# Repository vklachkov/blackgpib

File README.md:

# BlackGPIB

BlackGPIB is hardware that emulates GPIB disk drives for the GRiD Compass. It is based on the Raspberry Pi RP2040.

## Hardware

Hardware schematics and design files are located in the `hardware` folder. Production files are available in the [latest release](github.com/vklachkov/blackgpib/releases) on GitHub.

We recommend using the latest `pico` version. The list of components and known issues is described in the `README.md` file located in the `hardware/pico` directory.

## Firmware

The firmware source code is located in the `pico` folder.

The latest stable prebuilt firmware in UF2 format is available in the [latest release](https://github.com/vklachkov/blackgpib/releases) on GitHub.

### Flashing prebuilt firmware

To flash the firmware, hold the **BOOTSEL** button while connecting the Raspberry Pi Pico to your computer. The Pico will appear as a removable drive.

Copy the `blackgpib.uf2` file to this drive. The Pico will reboot automatically after the file is copied.

### Building firmware from source

To build the firmware yourself, install the Pico SDK first. Follow the instructions on the official Raspberry Pi website:

https://www.raspberrypi.com/documentation/microcontrollers/c_sdk.html

Then follow these steps.

1. Clone the repository:

```bash
git clone --depth 1 --recursive https://github.com/vklachkov/blackgpib
```

2. Go to the sources directory:

```bash
cd blackgpib/pico
```

3. Configure the project for your board:

```bash
cmake -S . -B build -DPICO_BOARD=pico
```

4. Build:

```bash
cmake --build build -j
```

5. Flash the firmware:

   Hold the **BOOTSEL** button while connecting the Raspberry Pi Pico to your computer. Then copy the `blackgpib.uf2` file from the `build` folder to the mounted Pico drive.

## How to use it?

After assembling and flashing the device, find a microSD card and format it as FAT32 or exFAT. Copy the disk images to this card. Insert the microSD card into BlackGPIB. Connect BlackGPIB to power, the LED should turn on after about one and a half seconds. After that, you can turn on the GRiD Compass. Enjoy!

### Which file formats are supported?

Currently, only .IMG files are supported. IMD and .CHD are not supported.

If you want to use IMD files from gridrepository.org, please use the [imd2raw](https://github.com/RetroFloppy/imd2raw) converter until BlackGPIB support is not available.

### How is the address selected?

For images that do not have a GPIB address specified in their filename, the address is selected automatically.

Floppy disk images use addresses 5, 6, and 13. Other images use the remaining default addresses (4, 5, 6, 12, 13).

If addresses conflict, or if there are no addresses left, an entry about this will be written to log.txt.

### How do I bind an image to a specific GPIB address?

Rename the image to FXX or HXX, where XX is the GPIB address. For example, FLOPPY4_TEST.IMG or HD12.IMG.

### How do I change the image geometry?

You can’t, it is selected automatically. Geometry configuration is not supported.

### Troubleshooting

**The LED is always off**

Check that you assembled the emulator correctly, powered it, and flashed the correct firmware.

**The device is steadily blinking the LED on the board**

This means that the device does not see the SD card, or the filesystem on it is not FAT.

Remove the SD card, format it again, and insert it into the device. If you did not disconnect power from BlackGPIB, then, if successful, the device will blink the LED several times, and then the LED should stay steadily on. This means that the device is ready to use.

**The device is blinking SOS**

This means that the device has gone into a boot loop. Normally, this should not happen.

Connect the device to your computer, open a serial port monitor, and check what went wrong before the boot loop. You can email me or open an issue, and I will try to help.

## License

This project is released under the [MIT License](LICENSE).

You are free to use, modify, and share it. I will be happy if BlackGPIB helps you bring your GRiD Compass back to life and use it again.

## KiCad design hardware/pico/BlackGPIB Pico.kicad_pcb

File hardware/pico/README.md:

# BlackGPIB Pico

## Components

| Part                     | Value                     | Package                  | Quantity | Comment                                                              |
|--------------------------|---------------------------|--------------------------|----------|----------------------------------------------------------------------|
| GPIB Connector Female    | -                         | 90 Degree                | 1        |                                                                      |
| SN75160                  | -                         | SMD or DIP               | 1        |                                                                      |
| SN75161 / SN75162        | -                         | SMD or DIP               | 1        |                                                                      |
| Resistor Pack (4x0603)   | 3.3kΩ                     | 1206 (4x0603)            | 2        | Front side of the board                                              |
| Resistor Pack (4x0603)   | 6.8kΩ                     | 1206 (4x0603)            | 2        | Back side of the board                                               |
| Ceramic Capacitor        | 0.1µF                     | 1206                     | 3        | Any for 5V, I used random 10V capacitor                              |
| Tantalum Capacitor       | 100µF                     | Case C (6032)            | 1        | Any for 3.3V, I used random 10V capacitor                            |
| MicroSD Card Slot        | -                         | SMD                      | 1        | [LSCS](https://www.lcsc.com/product-detail/C114218.html)             |
| Pi Pico 2040             | -                         | SMD                      | 1        |                                                                      |

## Known problems

### Rev 1

Because the Raspberry Pi Pico is positioned far from the edge of the board, not all micro-USB cables will fit.

When inserting the cable, hold it gently to prevent the SD card from popping out of the slot.

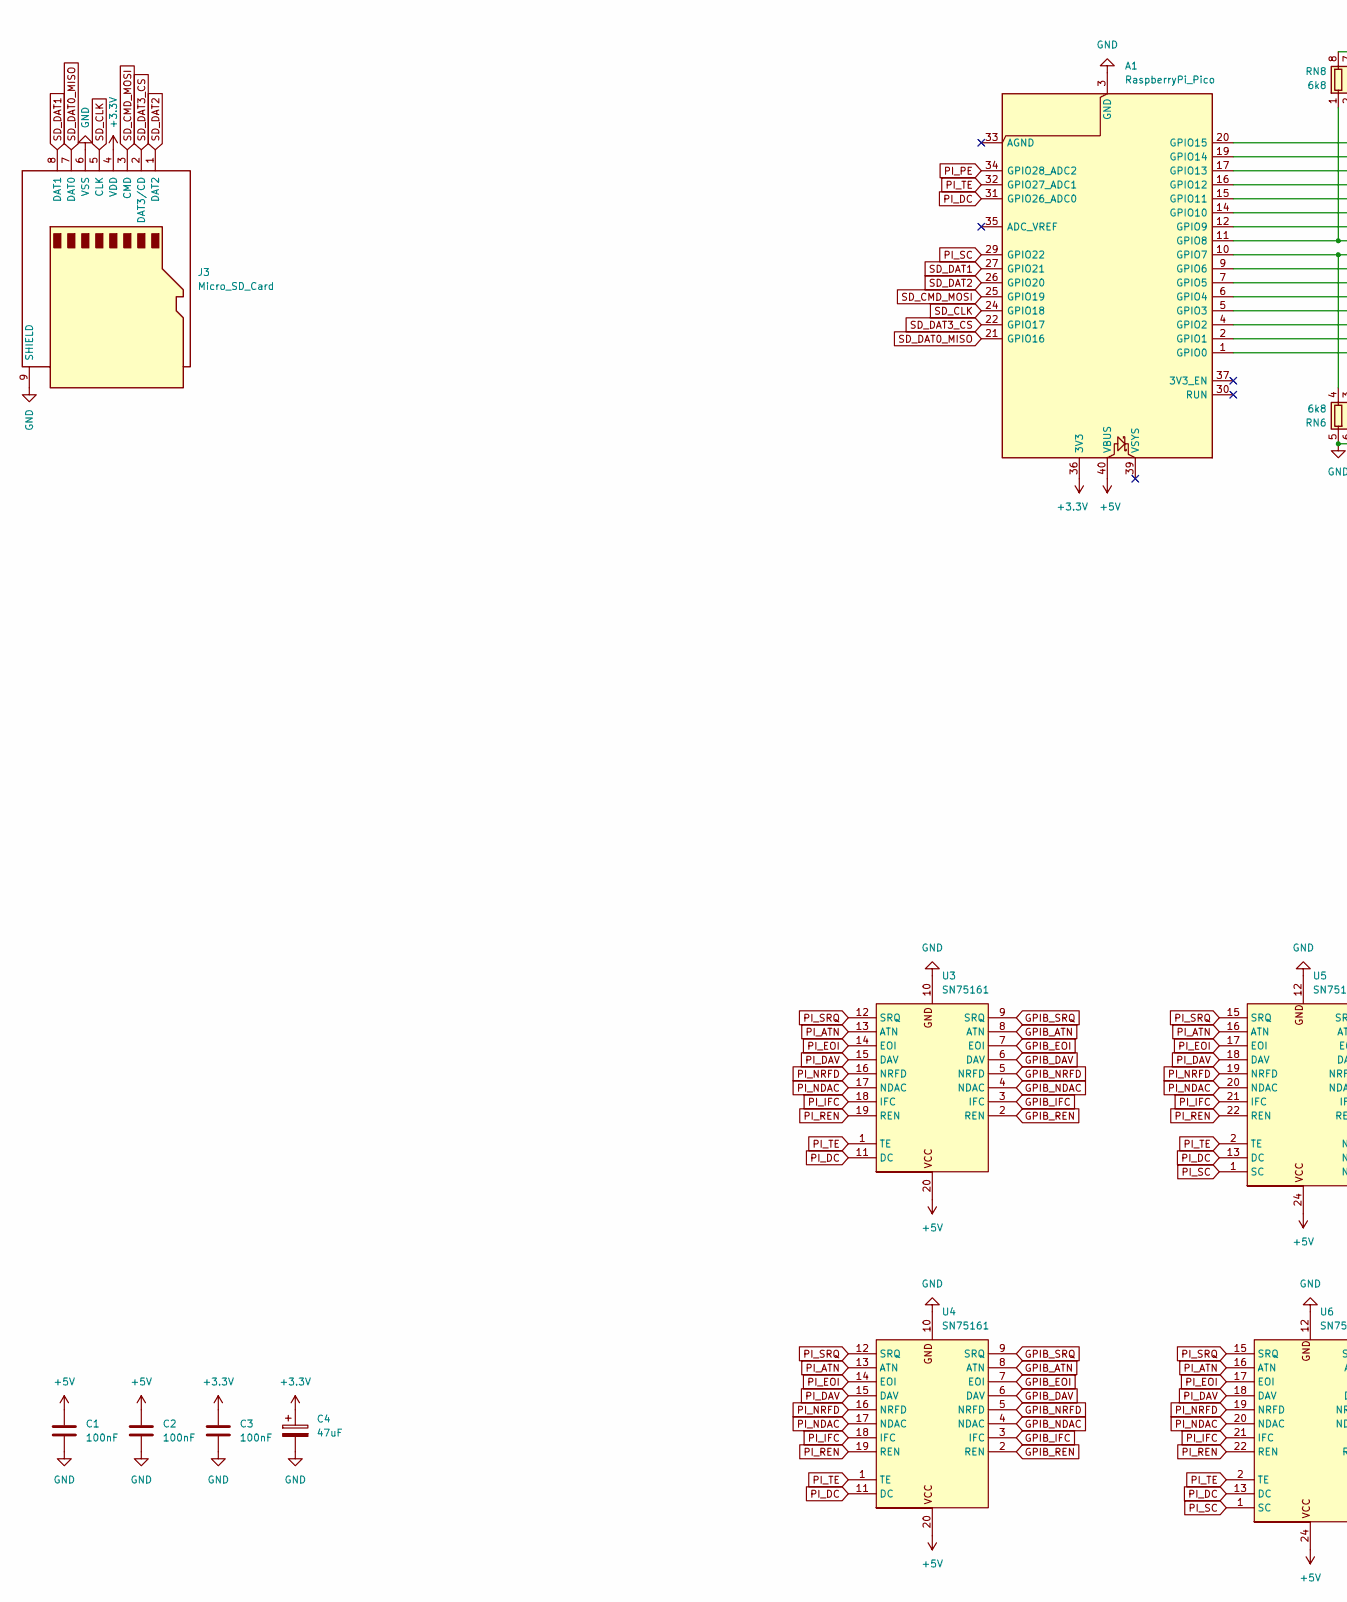
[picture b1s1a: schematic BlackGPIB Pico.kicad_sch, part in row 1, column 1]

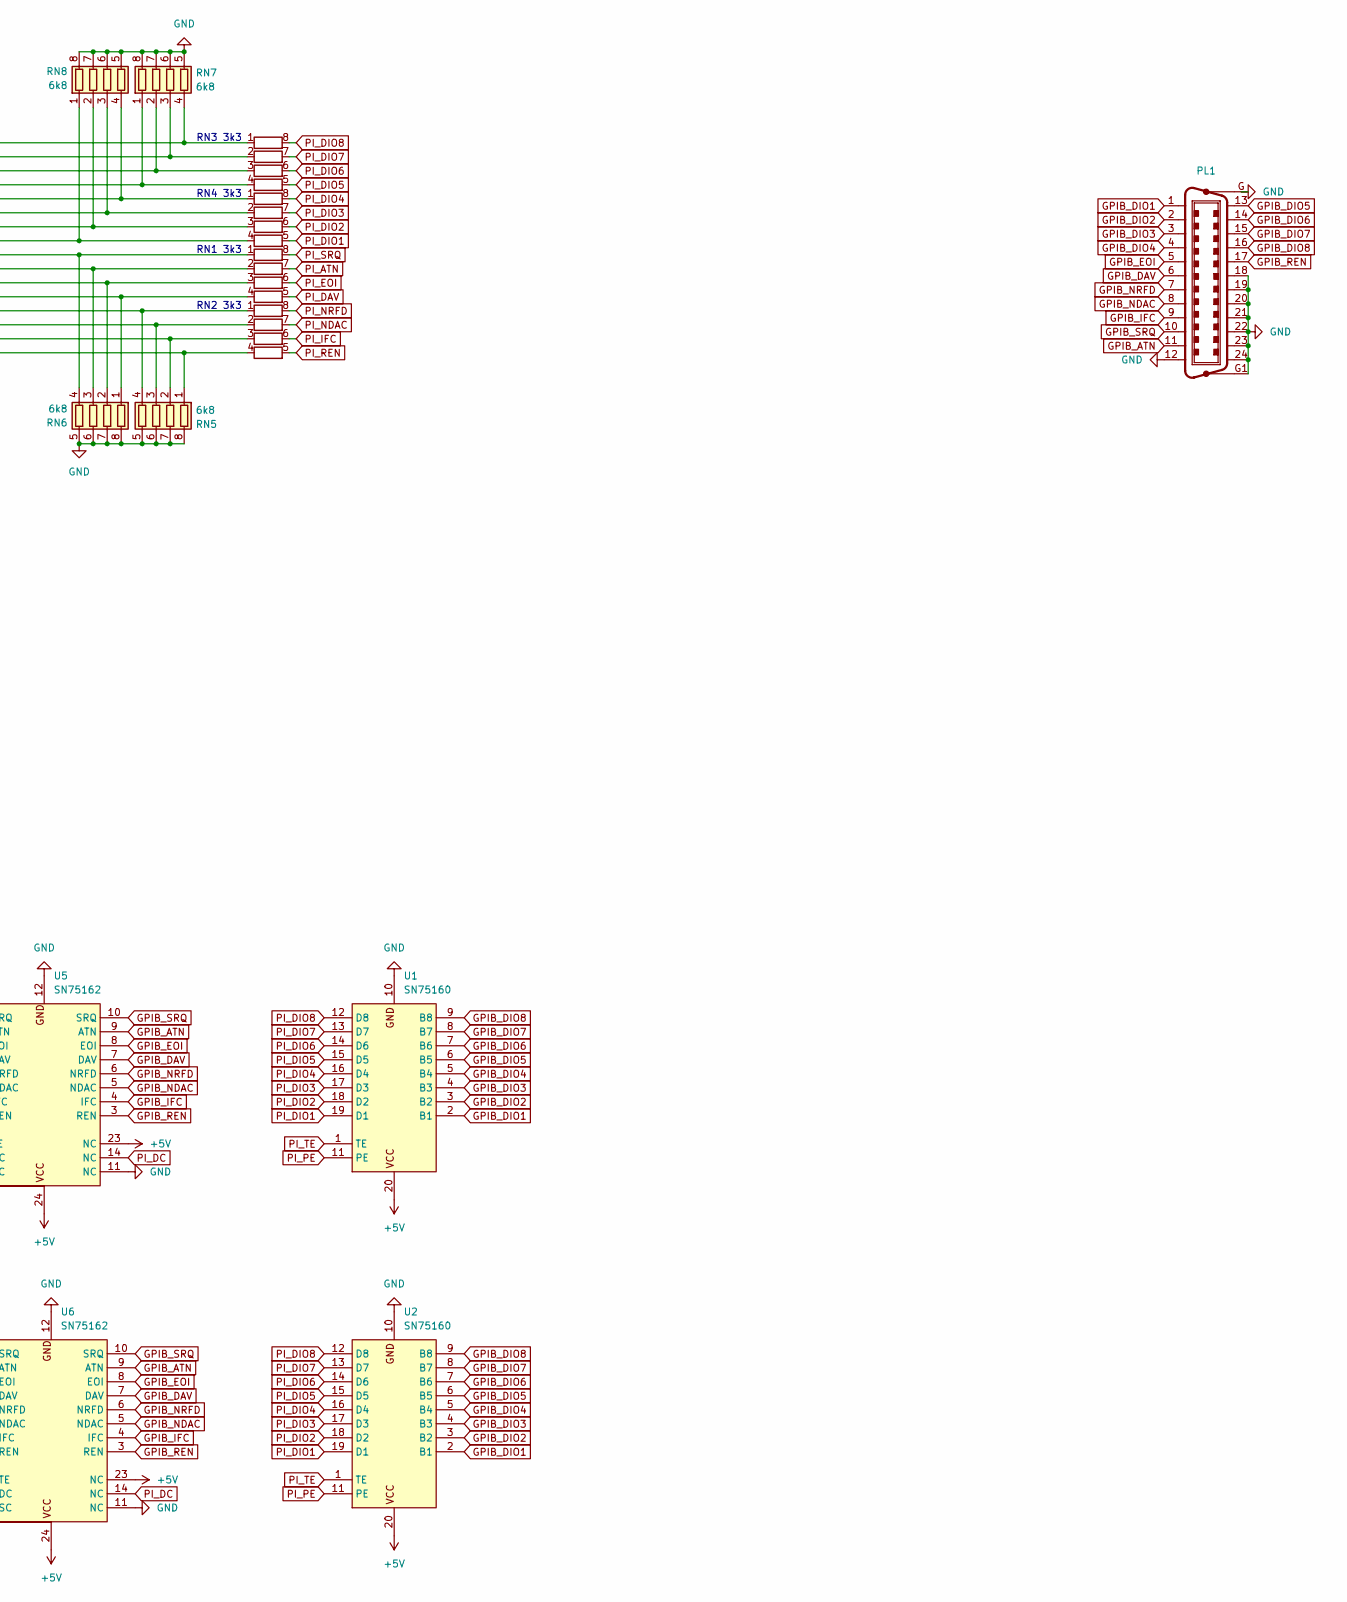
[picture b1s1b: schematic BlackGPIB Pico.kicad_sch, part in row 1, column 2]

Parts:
A1: RaspberryPi_Pico; RaspberryPi_Pico_SMD_HandSolder
C1, C2, C3: 100nF; C_1206_3216Metric_Pad1.33x1.80mm_HandSolder
C4: 47uF; CP_EIA-6032-15_Kemet-U_HandSolder
J3: Micro_SD_Card; microSD_HC_Hirose_DM3AT-SF-PEJM5
PL1: Centronics 24; Centronics-24
RN1, RN2, RN3, RN4: 3k3; R_Array_Convex_4x1206
RN5, RN6, RN7, RN8: 6k8; R_Array_Convex_4x1206
U1: SN75160; DIP-20_W7.62mm_LongPads
U2: SN75160; SOIC-20
U3: SN75161; DIP-20_W7.62mm_LongPads
U4: SN75161; SOIC-20
U5: SN75162; DIP-24_W7.62mm_LongPads
U6: SN75162; SOIC-24

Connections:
+3.3V: A1.36 (3V3), C3.1, C4.1, J3.4 (VDD)
+5V: A1.40 (VBUS), C1.1, C2.1, U1.20 (VCC), U2.20 (VCC), U3.20 (VCC), U4.20 (VCC), U5.23 (NC), U5.24 (VCC), U6.23 (NC), U6.24 (VCC)
GND: A1.3 (GND), A1.8 (GND), A1.13 (GND), A1.18 (GND), A1.23 (GND), A1.28 (GND), A1.38 (GND), C1.2, C2.2, C3.2, C4.2, J3.6 (VSS), J3.9 (SHIELD), PL1.12, PL1.18, PL1.19, PL1.20, PL1.21, PL1.22, PL1.23, PL1.24, PL1.G, PL1.G1, RN5.5 (R4.2), RN5.6 (R3.2), RN5.7 (R2.2), RN5.8 (R1.2), RN6.5 (R4.2), RN6.6 (R3.2), RN6.7 (R2.2), RN6.8 (R1.2), RN7.5 (R4.2), RN7.6 (R3.2), RN7.7 (R2.2), RN7.8 (R1.2), RN8.5 (R4.2), RN8.6 (R3.2), RN8.7 (R2.2), RN8.8 (R1.2), U1.10 (GND), U2.10 (GND), U3.10 (GND), U4.10 (GND), U5.11 (NC), U5.12 (GND), U6.11 (NC), U6.12 (GND)
GPIB_ATN: PL1.11, U3.8 (ATN), U4.8 (ATN), U5.9 (ATN), U6.9 (ATN)
GPIB_DAV: PL1.6, U3.6 (DAV), U4.6 (DAV), U5.7 (DAV), U6.7 (DAV)
GPIB_DIO1: PL1.1, U1.2 (B1), U2.2 (B1)
GPIB_DIO2: PL1.2, U1.3 (B2), U2.3 (B2)
GPIB_DIO3: PL1.3, U1.4 (B3), U2.4 (B3)
GPIB_DIO4: PL1.4, U1.5 (B4), U2.5 (B4)
GPIB_DIO5: PL1.13, U1.6 (B5), U2.6 (B5)
GPIB_DIO6: PL1.14, U1.7 (B6), U2.7 (B6)
GPIB_DIO7: PL1.15, U1.8 (B7), U2.8 (B7)
GPIB_DIO8: PL1.16, U1.9 (B8), U2.9 (B8)
GPIB_EOI: PL1.5, U3.7 (EOI), U4.7 (EOI), U5.8 (EOI), U6.8 (EOI)
GPIB_IFC: PL1.9, U3.3 (IFC), U4.3 (IFC), U5.4 (IFC), U6.4 (IFC)
GPIB_NDAC: PL1.8, U3.4 (NDAC), U4.4 (NDAC), U5.5 (NDAC), U6.5 (NDAC)
GPIB_NRFD: PL1.7, U3.5 (NRFD), U4.5 (NRFD), U5.6 (NRFD), U6.6 (NRFD)
GPIB_REN: PL1.17, U3.2 (REN), U4.2 (REN), U5.3 (REN), U6.3 (REN)
GPIB_SRQ: PL1.10, U3.9 (SRQ), U4.9 (SRQ), U5.10 (SRQ), U6.10 (SRQ)
unnamed: A1.1 (GPIO0), RN2.4 (R4.1), RN5.1 (R1.1)
unnamed: A1.2 (GPIO1), RN2.3 (R3.1), RN5.2 (R2.1)
unnamed: A1.4 (GPIO2), RN2.2 (R2.1), RN5.3 (R3.1)
unnamed: A1.5 (GPIO3), RN2.1 (R1.1), RN5.4 (R4.1)
unnamed: A1.6 (GPIO4), RN1.4 (R4.1), RN6.1 (R1.1)
unnamed: A1.7 (GPIO5), RN1.3 (R3.1), RN6.2 (R2.1)
unnamed: A1.9 (GPIO6), RN1.2 (R2.1), RN6.3 (R3.1)
unnamed: A1.10 (GPIO7), RN1.1 (R1.1), RN6.4 (R4.1)
unnamed: A1.11 (GPIO8), RN4.4 (R4.1), RN8.1 (R1.1)
unnamed: A1.12 (GPIO9), RN4.3 (R3.1), RN8.2 (R2.1)
unnamed: A1.14 (GPIO10), RN4.2 (R2.1), RN8.3 (R3.1)
unnamed: A1.15 (GPIO11), RN4.1 (R1.1), RN8.4 (R4.1)
unnamed: A1.16 (GPIO12), RN3.4 (R4.1), RN7.1 (R1.1)
unnamed: A1.17 (GPIO13), RN3.3 (R3.1), RN7.2 (R2.1)
unnamed: A1.19 (GPIO14), RN3.2 (R2.1), RN7.3 (R3.1)
unnamed: A1.20 (GPIO15), RN3.1 (R1.1), RN7.4 (R4.1)
PI_ATN: RN1.7 (R2.2), U3.13 (ATN), U4.13 (ATN), U5.16 (ATN), U6.16 (ATN)
PI_DAV: RN1.5 (R4.2), U3.15 (DAV), U4.15 (DAV), U5.18 (DAV), U6.18 (DAV)
PI_DC: A1.31 (GPIO26_ADC0), U3.11 (DC), U4.11 (DC), U5.13 (DC), U5.14 (NC), U6.13 (DC), U6.14 (NC)
PI_DIO1: RN4.5 (R4.2), U1.19 (D1), U2.19 (D1)
PI_DIO2: RN4.6 (R3.2), U1.18 (D2), U2.18 (D2)
PI_DIO3: RN4.7 (R2.2), U1.17 (D3), U2.17 (D3)
PI_DIO4: RN4.8 (R1.2), U1.16 (D4), U2.16 (D4)
PI_DIO5: RN3.5 (R4.2), U1.15 (D5), U2.15 (D5)
PI_DIO6: RN3.6 (R3.2), U1.14 (D6), U2.14 (D6)
PI_DIO7: RN3.7 (R2.2), U1.13 (D7), U2.13 (D7)
PI_DIO8: RN3.8 (R1.2), U1.12 (D8), U2.12 (D8)
PI_EOI: RN1.6 (R3.2), U3.14 (EOI), U4.14 (EOI), U5.17 (EOI), U6.17 (EOI)
PI_IFC: RN2.6 (R3.2), U3.18 (IFC), U4.18 (IFC), U5.21 (IFC), U6.21 (IFC)
PI_NDAC: RN2.7 (R2.2), U3.17 (NDAC), U4.17 (NDAC), U5.20 (NDAC), U6.20 (NDAC)
PI_NRFD: RN2.8 (R1.2), U3.16 (NRFD), U4.16 (NRFD), U5.19 (NRFD), U6.19 (NRFD)
PI_PE: A1.34 (GPIO28_ADC2), U1.11 (PE), U2.11 (PE)
PI_REN: RN2.5 (R4.2), U3.19 (REN), U4.19 (REN), U5.22 (REN), U6.22 (REN)
PI_SC: A1.29 (GPIO22), U5.1 (SC), U6.1 (SC)
PI_SRQ: RN1.8 (R1.2), U3.12 (SRQ), U4.12 (SRQ), U5.15 (SRQ), U6.15 (SRQ)
PI_TE: A1.32 (GPIO27_ADC1), U1.1 (TE), U2.1 (TE), U3.1 (TE), U4.1 (TE), U5.2 (TE), U6.2 (TE)
SD_CLK: A1.24 (GPIO18), J3.5 (CLK)
SD_CMD_MOSI: A1.25 (GPIO19), J3.3 (CMD)
SD_DAT0_MISO: A1.21 (GPIO16), J3.7 (DAT0)
SD_DAT1: A1.27 (GPIO21), J3.8 (DAT1)
SD_DAT2: A1.26 (GPIO20), J3.1 (DAT2)
SD_DAT3_CS: A1.22 (GPIO17), J3.2 (DAT3/CD)

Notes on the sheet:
RN2 3k3
RN3 3k3
RN4 3k3
RN1 3k3

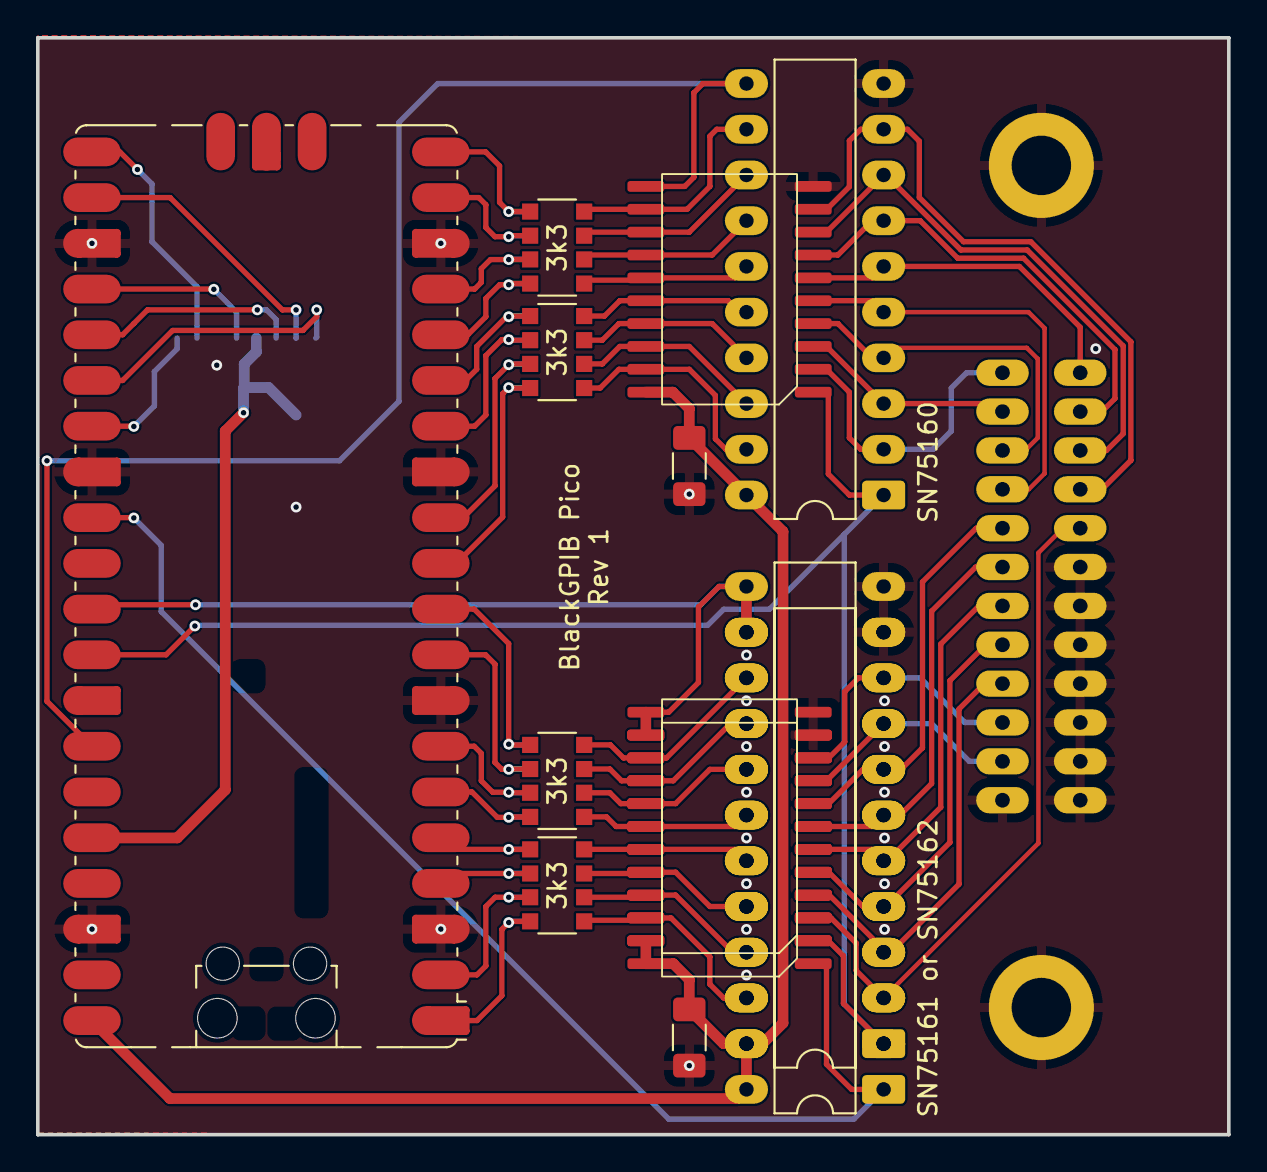
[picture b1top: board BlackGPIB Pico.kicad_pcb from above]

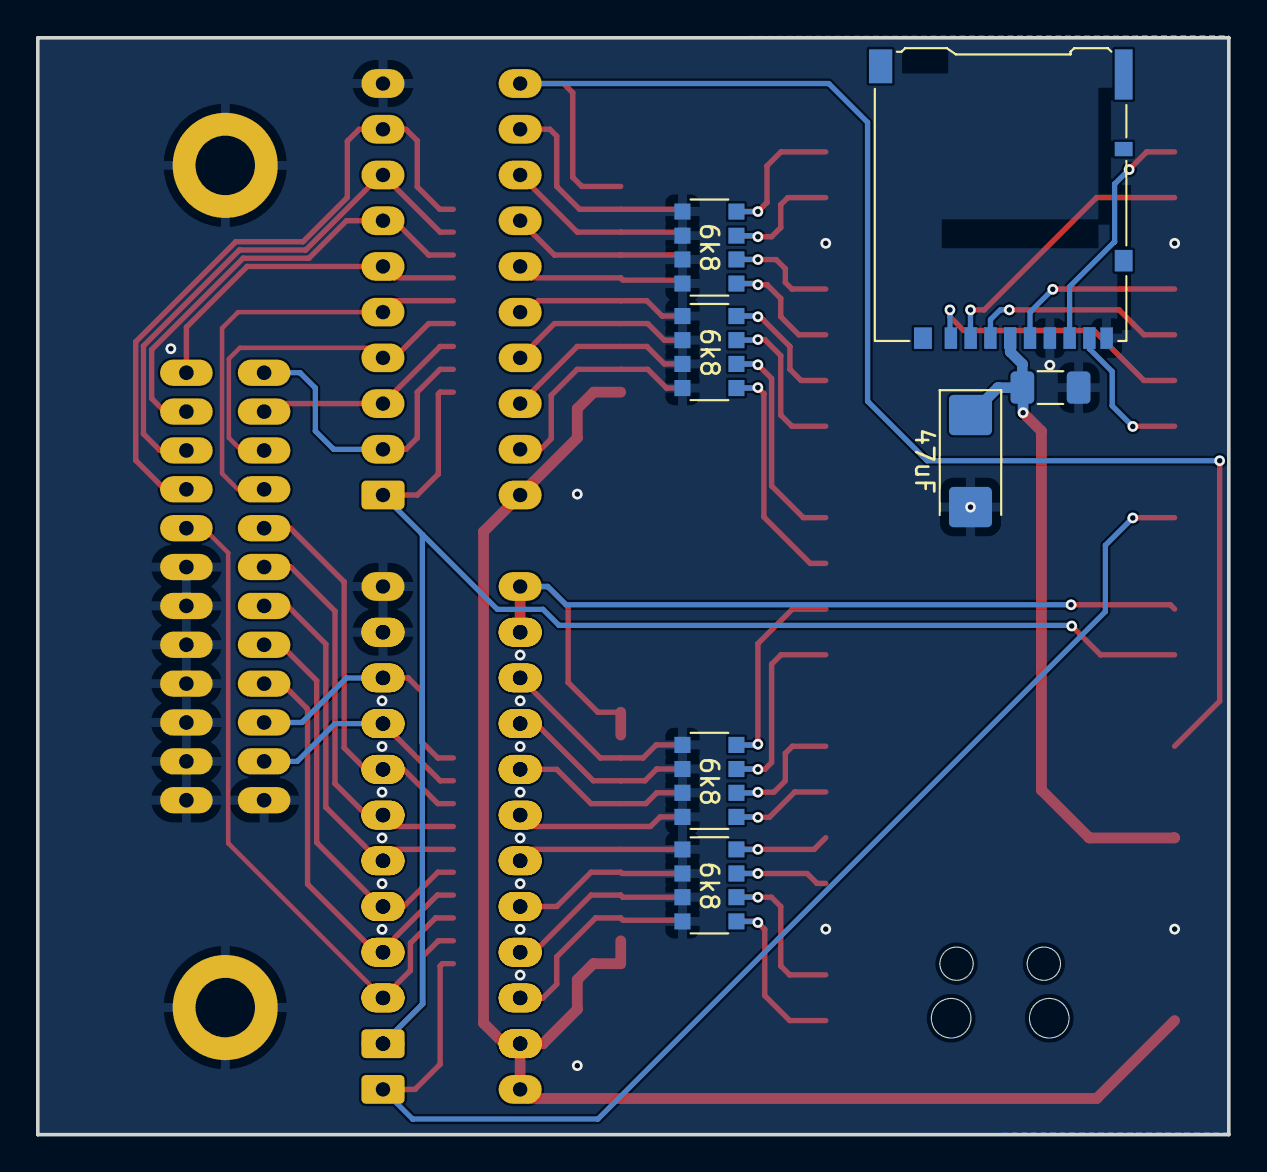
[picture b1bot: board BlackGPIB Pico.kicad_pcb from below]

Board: 2 copper layers, 66.2 x 60.9 mm, 21 parts (7 on the bottom side), 61 nets.

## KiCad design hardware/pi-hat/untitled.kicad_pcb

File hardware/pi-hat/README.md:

# First board by @JDat for Raspberry Pi 2+

This is the first revision of the board, designed by @JDat (also known as @YL3AKC):

In the photo, it's the old version with SRQ and ATN swapped.

## Components

| Part                  | Value                | Package    | Quantity |
|-----------------------|----------------------|------------|----------|
| GPIB Connector Female | -                    | 90 Degree  | 1        |
| SN75160               | -                    | SMD or DIP | 1        |
| SN75161/SN75162       | -                    | SMD or DIP | 1        |
| Resistor              | 3kΩ                  | 0805       | 20       |
| Capacitor             | 0.1uF                | 0805       | 2        |
| Pin Header            | 20x2 Straight Female | -          | 1        |

P.S. Instead of small SMD components, you can also use through-hole components, as Kirill @BOOtak Leyfer did.

https://t.me/bootaks_old_devices/286

## Errata

### Not enough space for the through-hole resistors.

As can be seen in Kirill's photo, the resistors are placed too close together, requiring them to be stacked on top of each other.

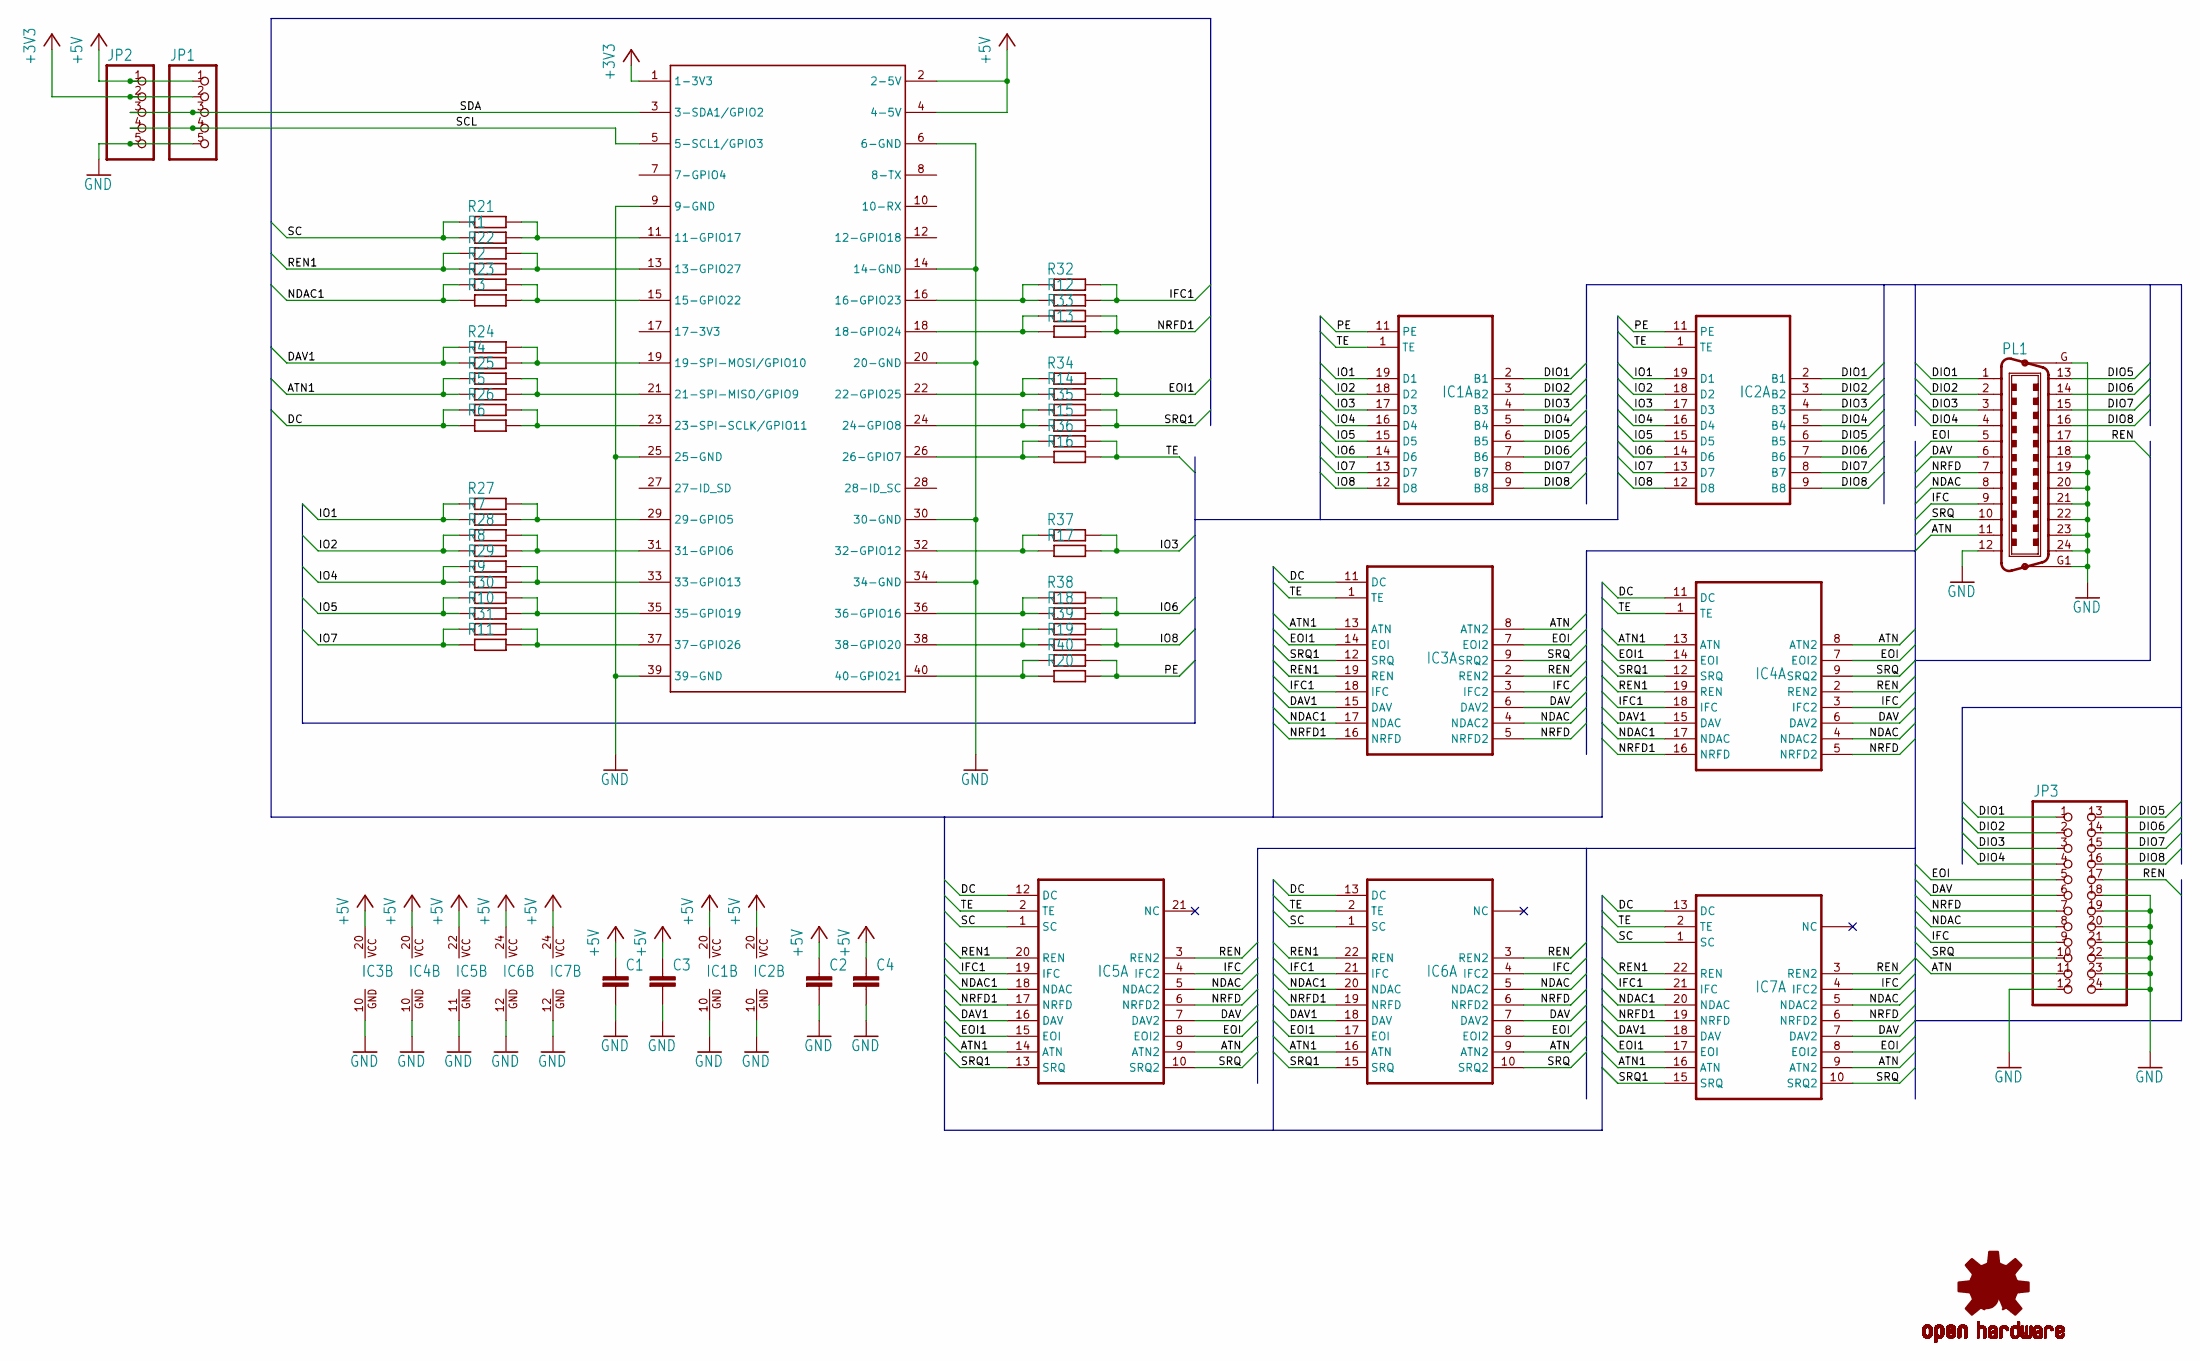
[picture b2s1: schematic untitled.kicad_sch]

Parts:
C1, C2: C-EUC0805; C0805
C3, C4: C-EU050-024X044; C050-024X044
IC1: 75160P; DIL20
IC2: 75160SO; SO20L
IC3: 75161P; DIL20
IC4: 75161SO; SO20L
IC5: 75162P; DIL22-3
IC6: 75162; DIL24-3
IC7: 75162SO24; SOIC127P1030X265-24N
JP1, JP2: PINHD-1X5; 1X05
JP3: GPIB-PINHD-2X12
LOGO2: OSHW-LOGOS; OSHW-LOGO-S
PL1: C24HP; 24HP
R1, R2, R3, R4, R5, R6, R7, R8, R9, R10, R11, R12, R13, R14, R15, R16, R17, R18, R19, R20: 3k; R0805
R21, R22, R23, R24, R25, R26, R27, R28, R29, R30, R31, R32, R33, R34, R35, R36, R37, R38, R39, R40: 3k; 0204_7
U$2: RASPBERRY-PI+HEADERONLY; RASPBERRY-PI-PLUS-HEADERONLY

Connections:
+3V3: JP1.2, JP2.2, U$2.1 (1-3V3)
+5V: C1.1, C2.1, C3.1, C4.1, IC1.20 (VCC), IC2.20 (VCC), IC3.20 (VCC), IC4.20 (VCC), IC5.22 (VCC), IC6.24 (VCC), IC7.24 (VCC), JP1.1, JP2.1, U$2.2 (2-5V), U$2.4 (4-5V)
/ATN: IC3.8 (ATN2), IC4.8 (ATN2), IC5.9 (ATN2), IC6.9 (ATN2), IC7.9 (ATN2), JP3.11, PL1.11
/ATN1: IC3.13 (ATN), IC4.13 (ATN), IC5.14 (ATN), IC6.16 (ATN), IC7.16 (ATN), R5.1, R25.1
/DAV: IC3.6 (DAV2), IC4.6 (DAV2), IC5.7 (DAV2), IC6.7 (DAV2), IC7.7 (DAV2), JP3.6, PL1.6
/DAV1: IC3.15 (DAV), IC4.15 (DAV), IC5.16 (DAV), IC6.18 (DAV), IC7.18 (DAV), R4.1, R24.1
/DC: IC3.11 (DC), IC4.11 (DC), IC5.12 (DC), IC6.13 (DC), IC7.13 (DC), R6.1, R26.1
/DIO1: IC1.2 (B1), IC2.2 (B1), JP3.1, PL1.1
/DIO2: IC1.3 (B2), IC2.3 (B2), JP3.2, PL1.2
/DIO3: IC1.4 (B3), IC2.4 (B3), JP3.3, PL1.3
/DIO4: IC1.5 (B4), IC2.5 (B4), JP3.4, PL1.4
/DIO5: IC1.6 (B5), IC2.6 (B5), JP3.13, PL1.13
/DIO6: IC1.7 (B6), IC2.7 (B6), JP3.14, PL1.14
/DIO7: IC1.8 (B7), IC2.8 (B7), JP3.15, PL1.15
/DIO8: IC1.9 (B8), IC2.9 (B8), JP3.16, PL1.16
/EOI: IC3.7 (EOI2), IC4.7 (EOI2), IC5.8 (EOI2), IC6.8 (EOI2), IC7.8 (EOI2), JP3.5, PL1.5
/EOI1: IC3.14 (EOI), IC4.14 (EOI), IC5.15 (EOI), IC6.17 (EOI), IC7.17 (EOI), R14.2, R34.2
/IFC: IC3.3 (IFC2), IC4.3 (IFC2), IC5.4 (IFC2), IC6.4 (IFC2), IC7.4 (IFC2), JP3.9, PL1.9
/IFC1: IC3.18 (IFC), IC4.18 (IFC), IC5.19 (IFC), IC6.21 (IFC), IC7.21 (IFC), R12.2, R32.2
/IO1: IC1.19 (D1), IC2.19 (D1), R7.1, R27.1
/IO2: IC1.18 (D2), IC2.18 (D2), R8.1, R28.1
/IO3: IC1.17 (D3), IC2.17 (D3), R17.2, R37.2
/IO4: IC1.16 (D4), IC2.16 (D4), R9.1, R29.1
/IO5: IC1.15 (D5), IC2.15 (D5), R10.1, R30.1
/IO6: IC1.14 (D6), IC2.14 (D6), R18.2, R38.2
/IO7: IC1.13 (D7), IC2.13 (D7), R11.1, R31.1
/IO8: IC1.12 (D8), IC2.12 (D8), R19.2, R39.2
/NDAC: IC3.4 (NDAC2), IC4.4 (NDAC2), IC5.5 (NDAC2), IC6.5 (NDAC2), IC7.5 (NDAC2), JP3.8, PL1.8
/NDAC1: IC3.17 (NDAC), IC4.17 (NDAC), IC5.18 (NDAC), IC6.20 (NDAC), IC7.20 (NDAC), R3.1, R23.1
/NRFD: IC3.5 (NRFD2), IC4.5 (NRFD2), IC5.6 (NRFD2), IC6.6 (NRFD2), IC7.6 (NRFD2), JP3.7, PL1.7
/NRFD1: IC3.16 (NRFD), IC4.16 (NRFD), IC5.17 (NRFD), IC6.19 (NRFD), IC7.19 (NRFD), R13.2, R33.2
/PE: IC1.11 (PE), IC2.11 (PE), R20.2, R40.2
/REN: IC3.2 (REN2), IC4.2 (REN2), IC5.3 (REN2), IC6.3 (REN2), IC7.3 (REN2), JP3.17, PL1.17
/REN1: IC3.19 (REN), IC4.19 (REN), IC5.20 (REN), IC6.22 (REN), IC7.22 (REN), R2.1, R22.1
/SC: IC5.1 (SC), IC6.1 (SC), IC7.1 (SC), R1.1, R21.1
/SCL: JP1.4, JP2.4, U$2.5 (5-SCL1/GPIO3)
/SDA: JP1.3, JP2.3, U$2.3 (3-SDA1/GPIO2)
/SRQ: IC3.9 (SRQ2), IC4.9 (SRQ2), IC5.10 (SRQ2), IC6.10 (SRQ2), IC7.10 (SRQ2), JP3.10, PL1.10
/SRQ1: IC3.12 (SRQ), IC4.12 (SRQ), IC5.13 (SRQ), IC6.15 (SRQ), IC7.15 (SRQ), R15.2, R35.2
/TE: IC1.1 (TE), IC2.1 (TE), IC3.1 (TE), IC4.1 (TE), IC5.2 (TE), IC6.2 (TE), IC7.2 (TE), R16.2, R36.2
GND: C1.2, C2.2, C3.2, C4.2, IC1.10 (GND), IC2.10 (GND), IC3.10 (GND), IC4.10 (GND), IC5.11 (GND), IC6.12 (GND), IC7.12 (GND), JP1.5, JP2.5, JP3.12, JP3.18, JP3.19, JP3.20, JP3.21, JP3.22, JP3.23, JP3.24, PL1.12, PL1.18, PL1.19, PL1.20, PL1.21, PL1.22, PL1.23, PL1.24, PL1.G, PL1.G1, U$2.6 (6-GND), U$2.9 (9-GND), U$2.14 (14-GND), U$2.20 (20-GND), U$2.25 (25-GND), U$2.30 (30-GND), U$2.34 (34-GND), U$2.39 (39-GND)
unnamed: R1.2, R21.2, U$2.11 (11-GPIO17)
unnamed: R2.2, R22.2, U$2.13 (13-GPIO27)
unnamed: R3.2, R23.2, U$2.15 (15-GPIO22)
unnamed: R12.1, R32.1, U$2.16 (16-GPIO23)
unnamed: R13.1, R33.1, U$2.18 (18-GPIO24)
unnamed: R4.2, R24.2, U$2.19 (19-SPI-MOSI/GPIO10)
unnamed: R5.2, R25.2, U$2.21 (21-SPI-MISO/GPIO9)
unnamed: R14.1, R34.1, U$2.22 (22-GPIO25)
unnamed: R6.2, R26.2, U$2.23 (23-SPI-SCLK/GPIO11)
unnamed: R15.1, R35.1, U$2.24 (24-GPIO8)
unnamed: R16.1, R36.1, U$2.26 (26-GPIO7)
unnamed: R7.2, R27.2, U$2.29 (29-GPIO5)
unnamed: R8.2, R28.2, U$2.31 (31-GPIO6)
unnamed: R17.1, R37.1, U$2.32 (32-GPIO12)
unnamed: R9.2, R29.2, U$2.33 (33-GPIO13)
unnamed: R10.2, R30.2, U$2.35 (35-GPIO19)
unnamed: R18.1, R38.1, U$2.36 (36-GPIO16)
unnamed: R11.2, R31.2, U$2.37 (37-GPIO26)
unnamed: R19.1, R39.1, U$2.38 (38-GPIO20)
unnamed: R20.1, R40.1, U$2.40 (40-GPIO21)

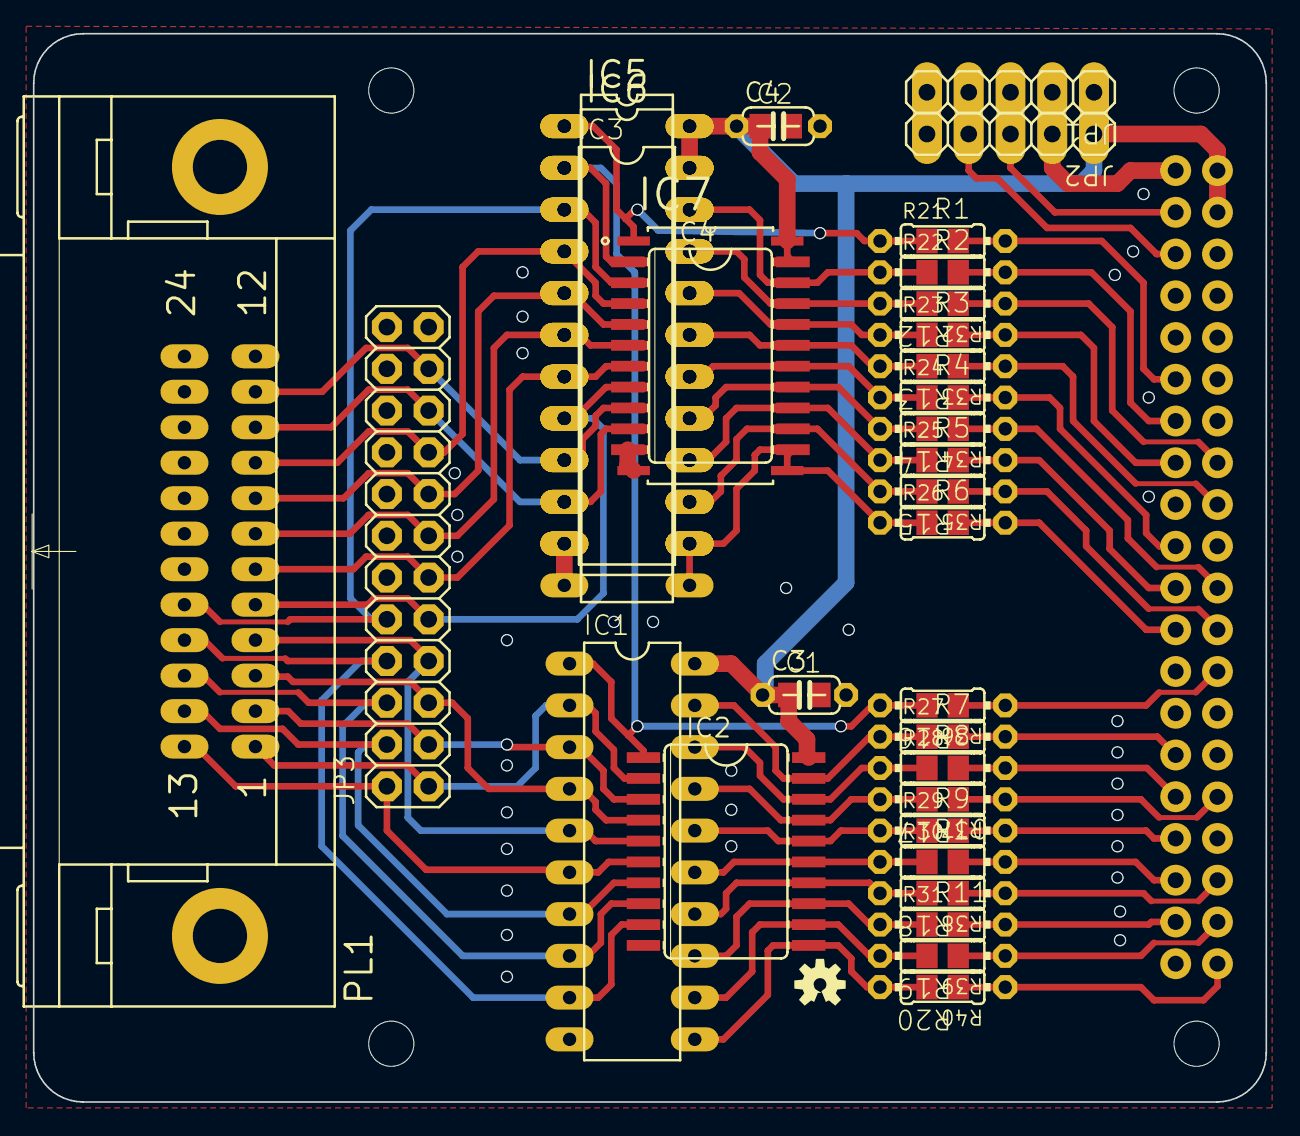
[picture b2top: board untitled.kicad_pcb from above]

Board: 2 copper layers, 75.0 x 65.0 mm, 61 parts (0 on the bottom side), 61 nets.

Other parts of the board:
UNK_HOLE_0: dummyfp0
UNK_HOLE_1: dummyfp1
UNK_HOLE_2: dummyfp2
UNK_HOLE_3: dummyfp3

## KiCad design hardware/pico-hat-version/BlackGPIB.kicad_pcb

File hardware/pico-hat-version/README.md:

An experimental version of the Pico-based emulator, but with the GPIB interface implemented on the [`hardware/pi-hat`](hardware/pi-hat) board. Unsupported by modern firmwares.

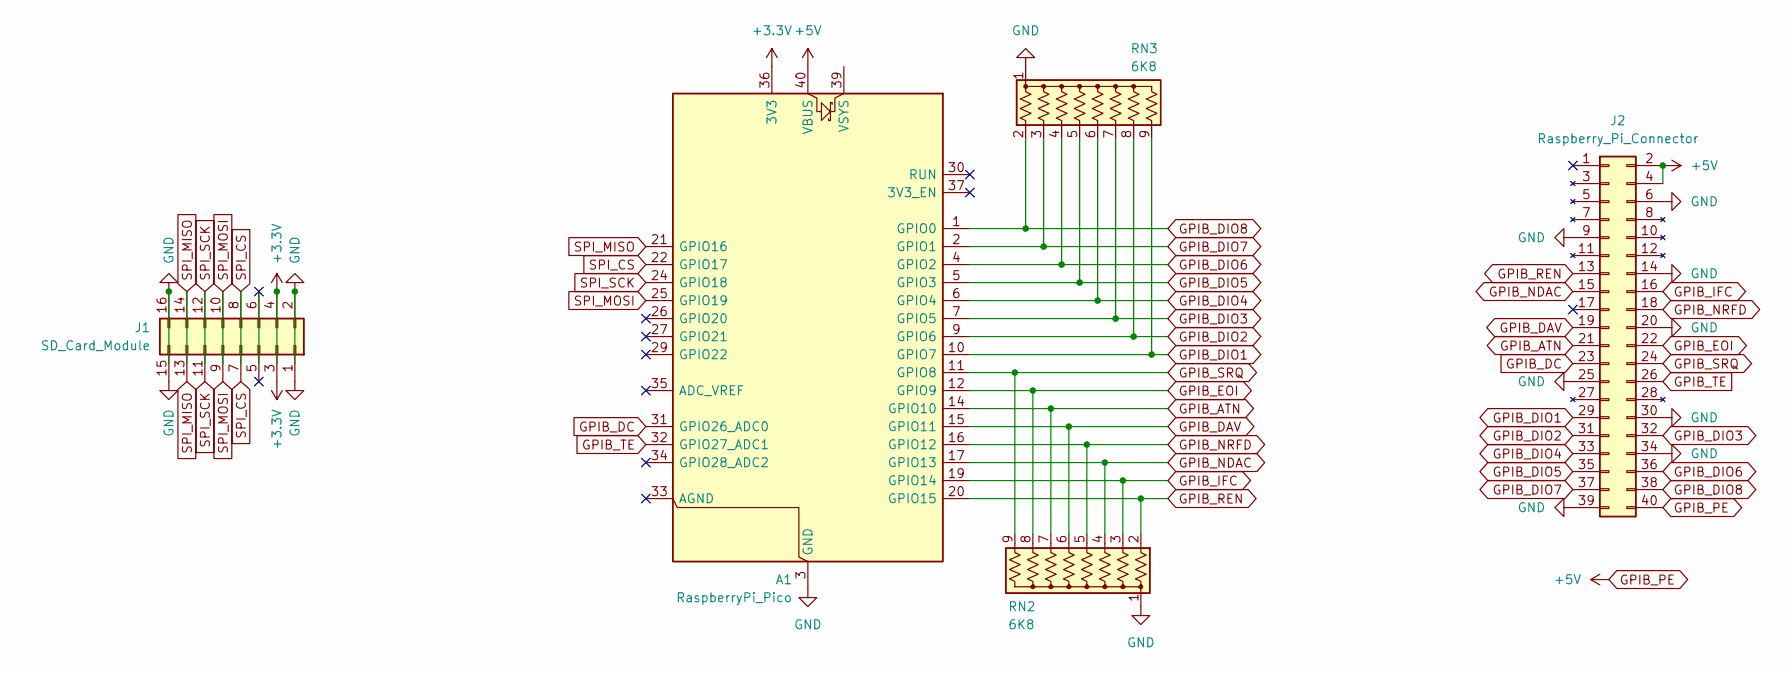
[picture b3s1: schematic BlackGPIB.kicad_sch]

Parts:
A1: RaspberryPi_Pico; RaspberryPi_Pico_W_SMD_HandSolder
J1: SD_Card_Module; PinHeader_2x08_P2.54mm_Vertical_SMD
J2: Raspberry_Pi_Connector; PinHeader_2x20_P2.54mm_Vertical_SMD
RN2: 6K8; PinHeader_1x09_P2.54mm_Horizontal_Right_FlipX
RN3: 6K8; PinHeader_1x09_P2.54mm_Horizontal_Right

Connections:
+3.3V: A1.36 (3V3), J1.3 (3.3V), J1.4 (3.3V)
GND: A1.3 (GND), A1.8 (GND), A1.13 (GND), A1.18 (GND), A1.23 (GND), A1.28 (GND), A1.38 (GND), J1.1 (GND), J1.2 (GND), J1.15 (GND), J1.16 (GND), J2.6 (GND), J2.9 (GND), J2.14 (GND), J2.20 (GND), J2.25 (GND), J2.30 (GND), J2.34 (GND), J2.39 (GND), RN2.1 (common), RN3.1 (common)
GPIB_ATN: A1.14 (GPIO10), J2.21 (ATN), RN2.7 (R6)
GPIB_DAV: A1.15 (GPIO11), J2.19 (DAV), RN2.6 (R5)
GPIB_DC: A1.31 (GPIO26_ADC0), J2.23 (DC)
GPIB_DIO1: A1.10 (GPIO7), J2.29 (DIO1), RN3.9 (R8)
GPIB_DIO2: A1.9 (GPIO6), J2.31 (DIO2), RN3.8 (R7)
GPIB_DIO3: A1.7 (GPIO5), J2.32 (DIO3), RN3.7 (R6)
GPIB_DIO4: A1.6 (GPIO4), J2.33 (DIO4), RN3.6 (R5)
GPIB_DIO5: A1.5 (GPIO3), J2.35 (DIO5), RN3.5 (R4)
GPIB_DIO6: A1.4 (GPIO2), J2.36 (DIO6), RN3.4 (R3)
GPIB_DIO7: A1.2 (GPIO1), J2.37 (DIO7), RN3.3 (R2)
GPIB_DIO8: A1.1 (GPIO0), J2.38 (DIO8), RN3.2 (R1)
GPIB_EOI: A1.12 (GPIO9), J2.22 (EOI), RN2.8 (R7)
GPIB_IFC: A1.19 (GPIO14), J2.16 (IFC), RN2.3 (R2)
GPIB_NDAC: A1.17 (GPIO13), J2.15 (NDAC), RN2.4 (R3)
GPIB_NRFD: A1.16 (GPIO12), J2.18 (NRFD), RN2.5 (R4)
GPIB_PE: A1.40 (VBUS), J2.2 (5V), J2.4 (5V), J2.40 (PE)
GPIB_REN: A1.20 (GPIO15), J2.13 (REN), RN2.2 (R1)
GPIB_SRQ: A1.11 (GPIO8), J2.24 (SRQ), RN2.9 (R8)
GPIB_TE: A1.32 (GPIO27_ADC1), J2.26 (TE)
SPI_CS: A1.22 (GPIO17), J1.7 (CS), J1.8 (CS)
SPI_MISO: A1.21 (GPIO16), J1.13 (MISO), J1.14 (MISO)
SPI_MOSI: A1.25 (GPIO19), J1.9 (MOSI), J1.10 (MOSI)
SPI_SCK: A1.24 (GPIO18), J1.11 (SCK), J1.12 (SCK)
